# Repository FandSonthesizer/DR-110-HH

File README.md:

# DR-110-HH

A sightly modified DR 110 clone, only Metal sounds.

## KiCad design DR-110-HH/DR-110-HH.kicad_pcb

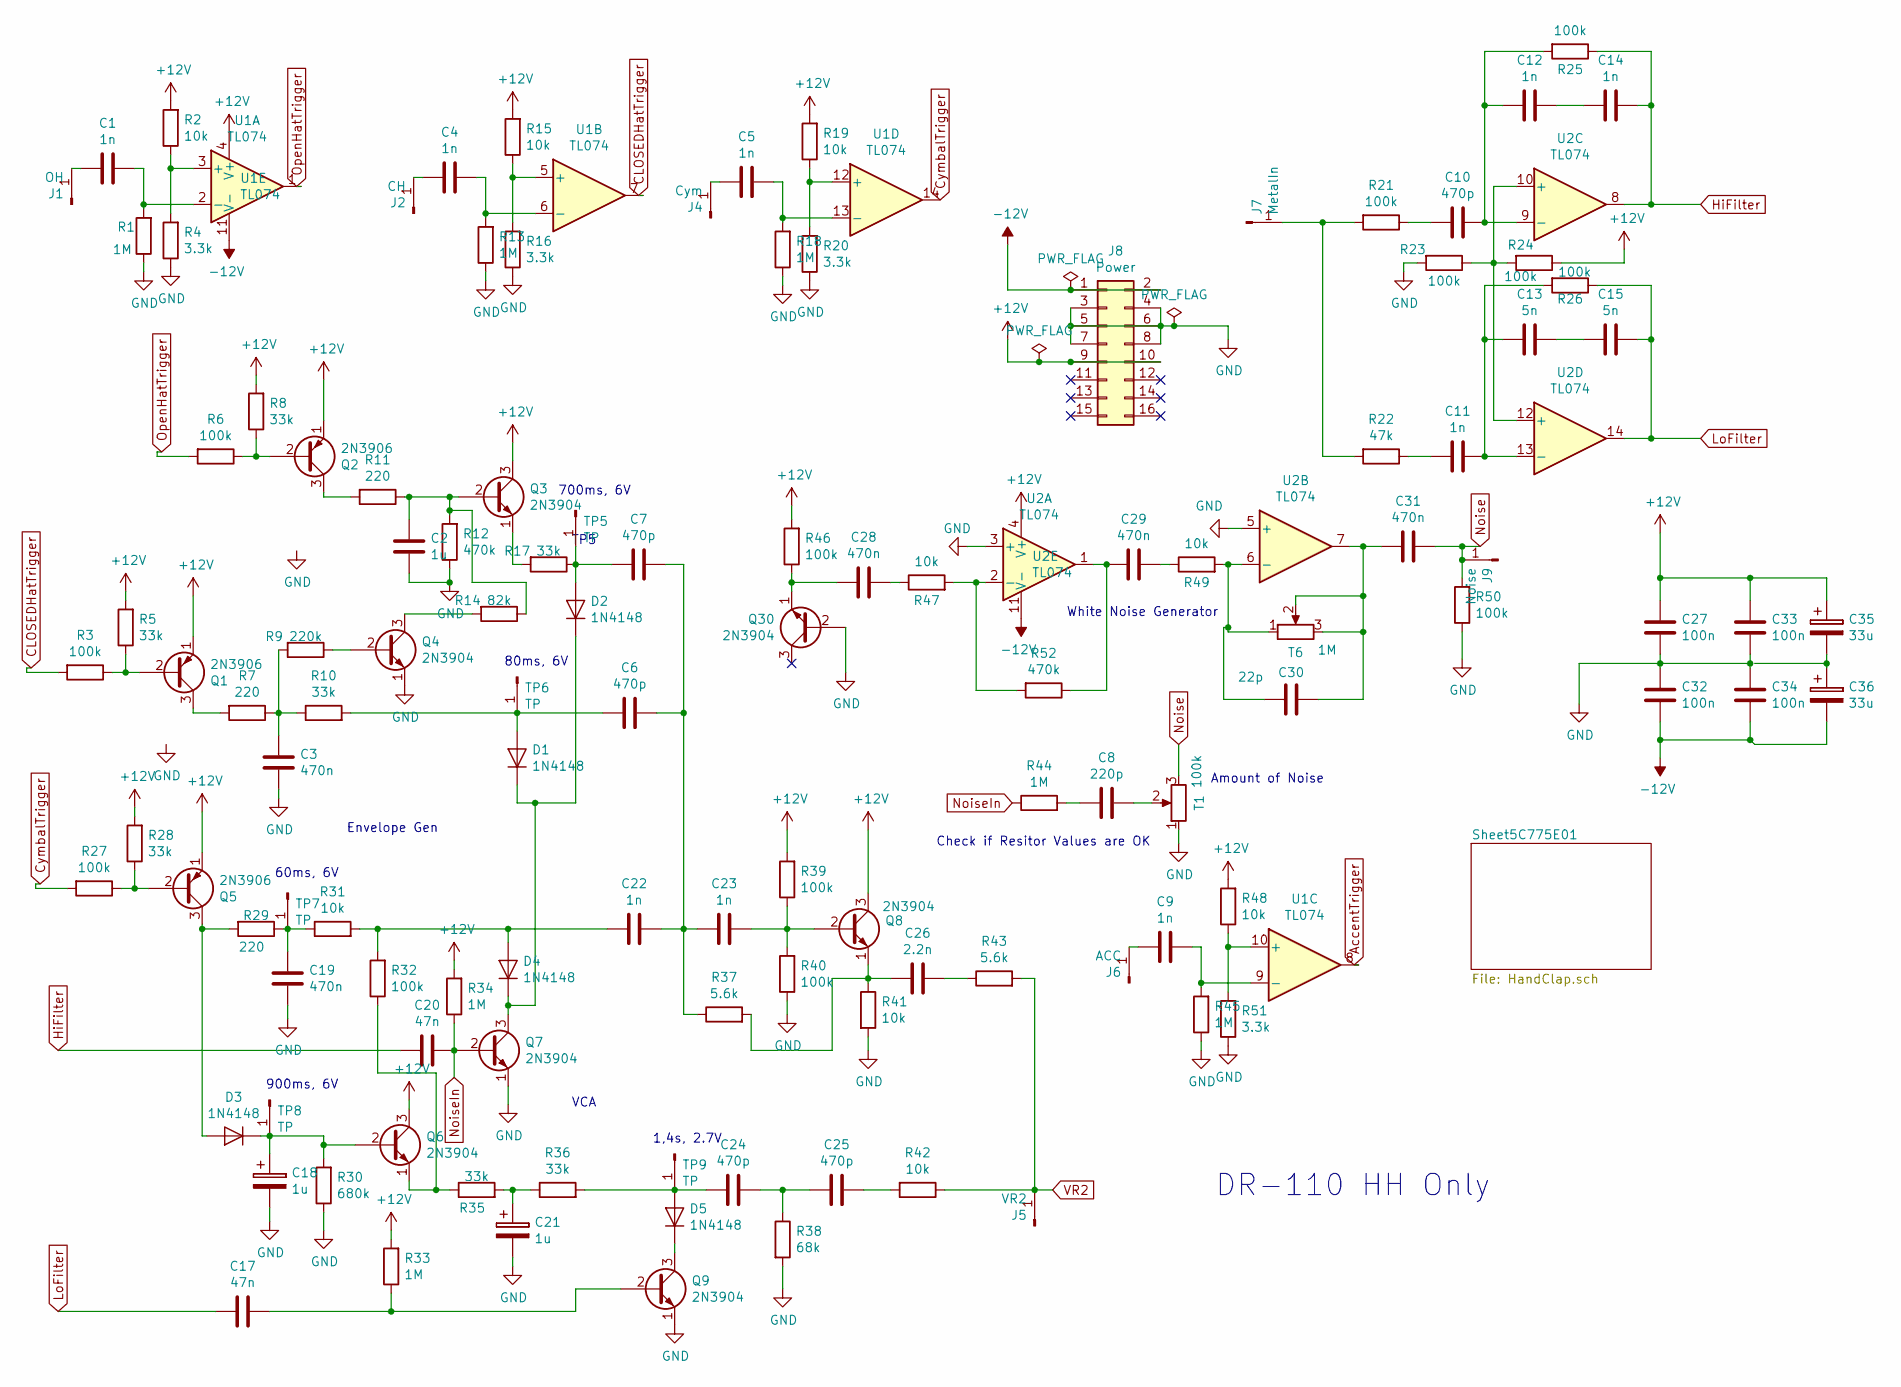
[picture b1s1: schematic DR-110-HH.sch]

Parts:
C1, C4, C5, C9, C11, C12, C14, C22, C23: 1n; Kondensator_Keramik
C2: 1u; Kondensator_Keramik
C3, C19, C28, C29, C31: 470n; Kondensator_Keramik
C6, C7, C10, C24, C25: 470p; Kondensator_Keramik
C8: 220p; Kondensator_Keramik
C13, C15: 5n; Kondensator_Keramik
C17, C20: 47n; Kondensator_Keramik
C18, C21: 1u; Elko_D6.3mm_P2.50mm
C26: 2.2n; Kondensator_Keramik
C27, C32, C33, C34: 100n; Kondensator_Keramik
C30: 22p; Kondensator_Keramik
C35, C36: 33u; Elko_D6.3mm_P2.50mm
D1, D2, D3, D4, D5: 1N4148; D_DO-35_SOD27_P7.62mm_Horizontal
J1: OH; Stift
J2: CH; Stift
J4: Cym; Stift
J5: VR2; Stift
J6: ACC; Stift
J7: MetalIn; Stift
J8: Power; PinSocket_2x08_P2.54mm_Vertical
J9: Noise; Stift
Q1, Q2, Q5: 2N3906; TO-92_Wide
Q3, Q4, Q6, Q7, Q8, Q9, Q30: 2N3904; TO-92_Wide
R1, R13, R18, R33, R34, R44, R45: 1M; Widerstand_liegend
R2, R15, R19, R31, R41, R42, R47, R48, R49: 10k; Widerstand_liegend
R3, R6, R21, R23, R24, R25, R26, R27, R32, R39, R40, R46, R50: 100k; Widerstand_liegend
R4, R16, R20, R51: 3.3k; Widerstand_liegend
R5, R8, R10, R17, R28, R35, R36: 33k; Widerstand_liegend
R7, R11, R29: 220; Widerstand_liegend
R9: 220k; Widerstand_liegend
R12, R52: 470k; Widerstand_liegend
R14: 82k; Widerstand_liegend
R22: 47k; Widerstand_liegend
R30: 680k; Widerstand_liegend
R37, R43: 5.6k; Widerstand_liegend
R38: 68k; Widerstand_liegend
T1: 100k; Trimmer_Vertical
T6: 1M; Trimmer_Vertical
TP5, TP6, TP7, TP8, TP9: TP; Stift
U1, U2: TL074; DIP-14_W7.62mm_Socket_LongPads

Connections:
+12V: C27.2, C33.2, C35.1, J8.9, J8.10, Q1.1 (E), Q2.1 (E), Q3.3 (C), Q5.1 (E), Q6.3 (C), Q8.3 (C), R2.2, R5.2, R8.2, R15.2, R19.2, R24.1, R28.2, R33.2, R34.2, R39.2, R46.2, R48.2, U1.4 (V+), U2.4 (V+); also elsewhere on the board
-12V: C32.1, C34.1, C36.2, J8.1, J8.2, U1.11 (V-), U2.11 (V-)
AccentTrigger: U1.8; also elsewhere on the board
CLOSEDHatTrigger: R3.2, U1.7
CymbalTrigger: R27.2, U1.14
GND: C2.1, C3.1, C18.2, C19.1, C21.2, C27.1, C32.2, C33.1, C34.2, J8.3, J8.4, J8.5, J8.6, J8.7, J8.8, Q4.1 (E), Q7.1 (E), Q9.1 (E), Q30.2 (B), R1.1, R4.1, R12.1, R13.1, R16.1, R18.1, R20.1, R23.2, R30.1, R38.2, R40.1, R41.2, R45.1, R50.1, R51.1, T1.1, U2.3 (+), U2.5 (+); also elsewhere on the board
HiFilter: C14.1, C20.2, R25.1, U2.8
LoFilter: C15.1, C17.1, R26.1, U2.14
unnamed: C1.1, R1.2, U1.2 (-)
unnamed: C1.2, J1.1
unnamed: C2.2, Q3.2 (B), R11.1, R12.2, R14.1
unnamed: C3.2, R7.1, R9.2, R10.1
unnamed: C4.1, R13.2, U1.6 (-)
unnamed: C4.2, J2.1
unnamed: C5.1, R18.2, U1.13 (-)
unnamed: C5.2, J4.1
unnamed: C6.2, D1.2 (A), R10.2, TP6.1
unnamed: C7.2, D2.2 (A), R17.1, TP5.1
unnamed: C8.1, T1.2
unnamed: C8.2, R44.2
unnamed: C9.1, R45.2, U1.9 (-)
unnamed: C9.2, J6.1
unnamed: C10.1, C12.2, R25.2, U2.9 (-)
unnamed: C10.2, R21.1
unnamed: C11.1, C13.2, R26.2, U2.13 (-)
unnamed: C11.2, R22.1
unnamed: C12.1, C14.2
unnamed: C13.1, C15.2
unnamed: C17.2, Q9.2 (B), R33.1
unnamed: C18.1, D3.1 (K), Q6.2 (B), R30.2, TP8.1
unnamed: C19.2, R29.1, R31.1, TP7.1
unnamed: C21.1, R35.2, R36.1
unnamed: C6.1, C7.1, C22.1, C23.2, R37.1
unnamed: C22.2, D4.2 (A), R31.2, R32.2
unnamed: C23.1, Q8.2 (B), R39.1, R40.2
unnamed: C24.1, C25.2, R38.1
unnamed: C24.2, D5.2 (A), R36.2, TP9.1
unnamed: C25.1, R42.2
unnamed: C26.1, R43.1
unnamed: C26.2, Q8.1 (E), R37.2, R41.1
unnamed: C28.1, R47.1
unnamed: C28.2, Q30.1 (E), R46.1
unnamed: C29.1, R49.1
unnamed: C29.2, R52.1, U2.1
unnamed: C30.1, C31.2, T6.2, T6.3, U2.7
unnamed: C30.2, R49.2, T6.1, U2.6 (-)
unnamed: C35.2, C36.1
unnamed: D1.1 (K), D2.1 (K), D4.1 (K), Q7.3 (C)
unnamed: D3.2 (A), Q5.3 (C), R29.2
unnamed: D5.1 (K), Q9.3 (C)
unnamed: J7.1, R21.2, R22.2
unnamed: Q1.2 (B), R3.1, R5.1
unnamed: Q1.3 (C), R7.2
unnamed: Q2.2 (B), R6.1, R8.1
unnamed: Q2.3 (C), R11.2
unnamed: Q3.1 (E), R17.2
unnamed: Q4.2 (B), R9.1
unnamed: Q4.3 (C), R14.2
unnamed: Q5.2 (B), R27.1, R28.1
unnamed: Q6.1 (E), R32.1, R35.1
unnamed: R2.1, R4.2, U1.3 (+)
unnamed: R15.1, R16.2, U1.5 (+)
unnamed: R19.1, R20.2, U1.12 (+)
unnamed: R23.1, R24.2, U2.10 (+), U2.12 (+)
unnamed: R47.2, R52.2, U2.2 (-)
unnamed: R48.1, R51.2, U1.10 (+)
Noise: C31.1, J9.1, R50.2, T1.3
NoiseIn: C20.1, Q7.2 (B), R34.1, R44.1
OpenHatTrigger: R6.2, U1.1
VR2: J5.1, R42.1, R43.2; also elsewhere on the board

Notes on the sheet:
White Noise Generator
Envelope Gen
VCA
TP5
700ms, 6V
80ms, 6V
60ms, 6V
900ms, 6V
1,4s, 2.7V
DR-110 HH Only
Amount of Noise
Check if Resitor Values are OK

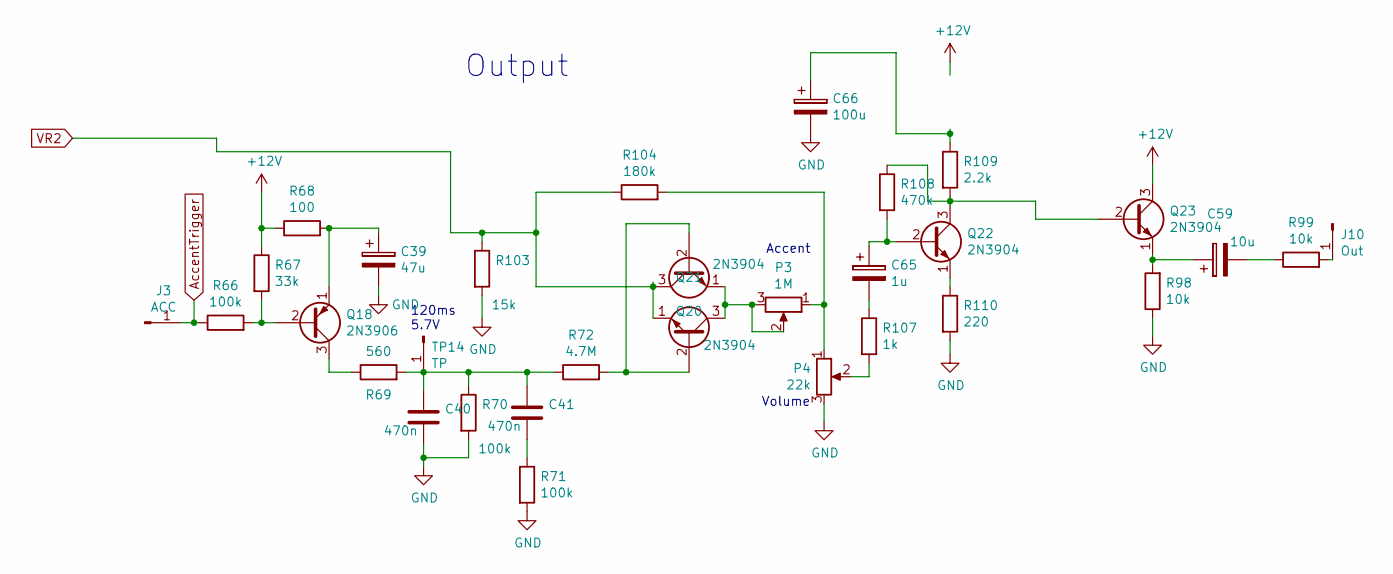
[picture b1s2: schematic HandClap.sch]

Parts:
C39: 47u; Elko_D6.3mm_P2.50mm
C40, C41: 470n; Kondensator_Keramik
C59: 10u; Elko_D6.3mm_P2.50mm
C65: 1u; Elko_D6.3mm_P2.50mm
C66: 100u; Elko_D6.3mm_P2.50mm
J3: ACC; Stift
J10: Out; Stift
P3: 1M; Trimmer_Vertical
P4: 22k; Trimmer_Vertical
Q18: 2N3906; TO-92_Wide
Q20, Q21, Q22, Q23: 2N3904; TO-92_Wide
R66, R70, R71: 100k; Widerstand_liegend
R67: 33k; Widerstand_liegend
R68: 100; Widerstand_liegend
R69: 560; Widerstand_liegend
R72: 4.7M; Widerstand_liegend
R98, R99: 10k; Widerstand_liegend
R103: 15k; Widerstand_liegend
R104: 180k; Widerstand_liegend
R107: 1k; Widerstand_liegend
R108: 470k; Widerstand_liegend
R109: 2.2k; Widerstand_liegend
R110: 220; Widerstand_liegend
TP14: TP; Stift

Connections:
+12V: Q23.3 (C), R67.1, R68.1; also elsewhere on the board
AccentTrigger: J3.1, R66.1; also elsewhere on the board
GND: C39.2, C40.2, C66.2, P4.3, R70.2, R71.2, R98.1, R103.2, R110.2; also elsewhere on the board
unnamed: C39.1, Q18.1 (E), R68.2
unnamed: C40.1, C41.1, R69.2, R70.1, R72.1, TP14.1
unnamed: C41.2, R71.1
unnamed: C59.1, Q23.1 (E), R98.2
unnamed: C59.2, R99.1
unnamed: C65.1, Q22.2 (B), R108.2
unnamed: C65.2, R107.1
unnamed: C66.1, R109.1
unnamed: J10.1, R99.2
unnamed: P3.1, P4.1, R104.2
unnamed: P3.2, P3.3, Q20.1 (E), Q21.3 (C)
unnamed: P4.2, R107.2
unnamed: Q18.2 (B), R66.2, R67.2
unnamed: Q18.3 (C), R69.1
unnamed: Q20.2 (B), Q21.2 (B), R72.2
unnamed: Q22.1 (E), R110.1
unnamed: Q22.3 (C), Q23.2 (B), R108.1, R109.2
VR2: Q20.3 (C), Q21.1 (E), R103.1, R104.1; also elsewhere on the board

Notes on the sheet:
Accent
Volume
120ms 5.7V
Output

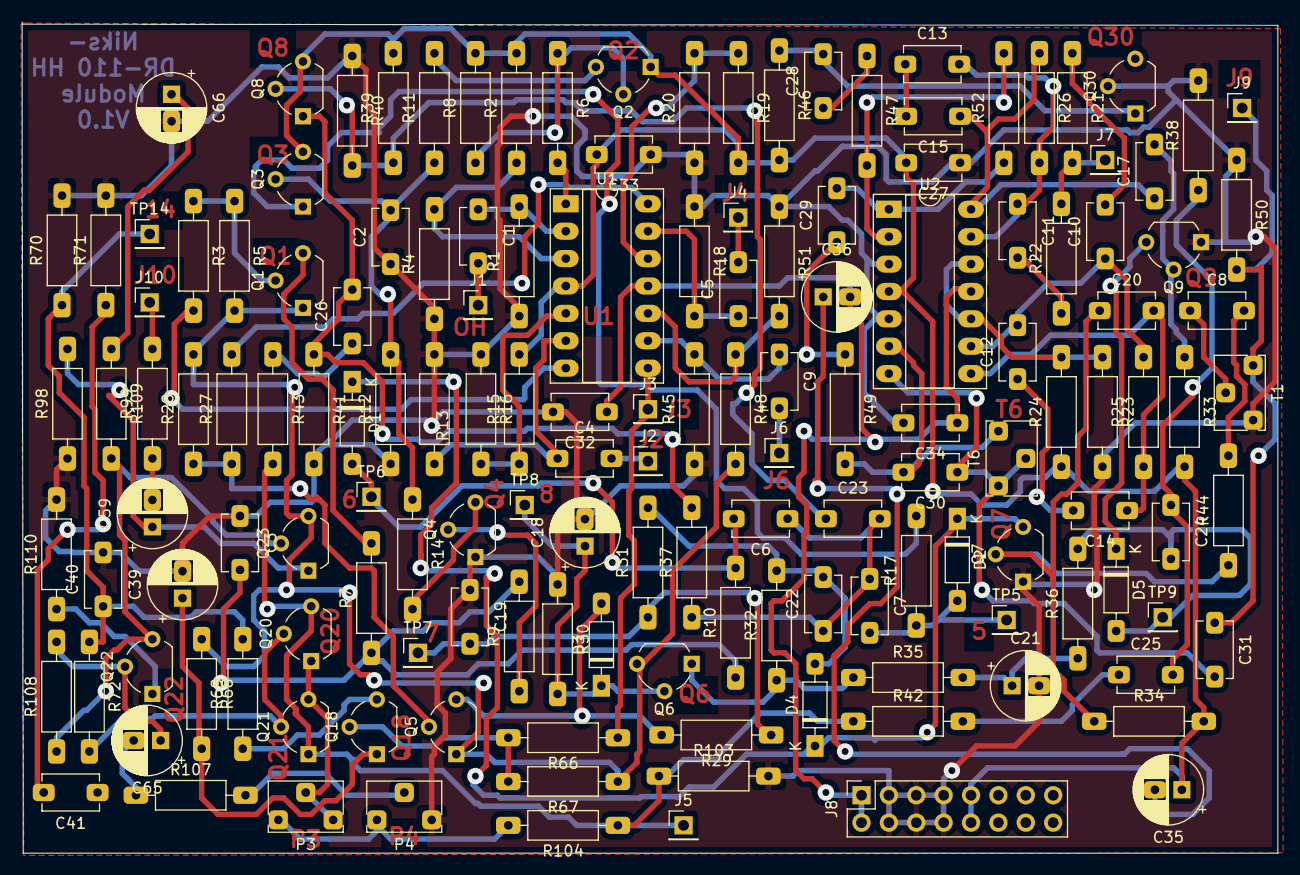
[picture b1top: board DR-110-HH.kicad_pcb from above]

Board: 2 copper layers, 116.5 x 77.1 mm, 150 parts (0 on the bottom side), 87 nets.
